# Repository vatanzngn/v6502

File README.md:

# 💻 vz6502: A Homebrew Single Board Computer Based on WDC 65C02

A custom-built single board computer (SBC) powered by the WDC 65C02 processor, featuring VGA and PS/2 interfaces, an onboard terminal, and a CPLD-based system controller.

---

## ⚙️ Specifications

- **CPU:** WDC 65C02 @ 1.8432 MHz (chosen for UART-compatible clock rate)
- **System Controller:** Altera EPM7128SLC84 CPLD
- **ROM:** Atmel 28C256 EEPROM (16 KB used)
- **RAM:** Hitachi 62256 SRAM (28 KB used)
- **Serial Interfaces:**  
  - 2× 65C51 ACIA (UART and terminal communication)
- **I/O Interface:**  
  - 1× 65C22 VIA
- **Video Output:** VGA interface  
- **Input:** PS/2 keyboard  
- **Terminal:** Atmega328P-based serial terminal

## 🧩 PCB Design

<div align="center">
  
  <p><em>Front side of the PCB</em></p>
</div>

<div align="center">
  
  <p><em>Back side of the PCB</em></p>
</div>

## 🔌 Schematic

<div align="center">
  
  <p><em>System schematic showing CPU, RAM, ROM, I/O, and video interfaces</em></p>
</div>

## 🧠 Memory Map Overview

### 📋 Detailed Address Mapping

| Unit   | First Address (bin)          | Last Address (bin)           | Address Range (Hex) | Description            | Size  |
|--------|------------------------------|------------------------------|---------------------|------------------------|-------|
| RAM    | 0000 0000 0000 0000          | 0110 1111 1111 1111          | 0000–6FFF           | System memory          | 28 KB |
| VIA0   | 0111 0000 0000 0000          | 0111 0000 0000 1100          | 7000–700C           | VIA 0 registers        | 12 B  |
| VIA1   | 0111 0001 0000 0000          | 0111 0001 0000 1100          | 7100–710C           | VIA 1 registers        | 12 B  |
| ACIA0  | 0111 0010 0000 0000          | 0111 0010 0000 0011          | 7200–7203           | ACIA 0 registers       | 4 B   |
| ACIA1  | 0111 0011 0000 0000          | 0111 0011 0000 0011          | 7300–7303           | ACIA 1 registers       | 4 B   |
| RESRV  | 0111 0100 0000 0000          | 0111 1111 1111 1111          | 7304–7FFF           | Reserved               | N/A   |
| ROM    | 1000 0000 0000 0000          | 1111 1111 1111 1111          | 8000–FFFF           | System ROM             | 32 KB |

---

## 📁 File Structure

| Folder   | Description                        |
|----------|------------------------------------|
| `/pcb`   | KiCAD PCB design files             |
| `/gerber`| Gerber files for PCB manufacturing |
| `/ext`   | GitHub assets, images, and extras  |

---
⚠️ CPLD and operating system source files will be uploaded in a future update.

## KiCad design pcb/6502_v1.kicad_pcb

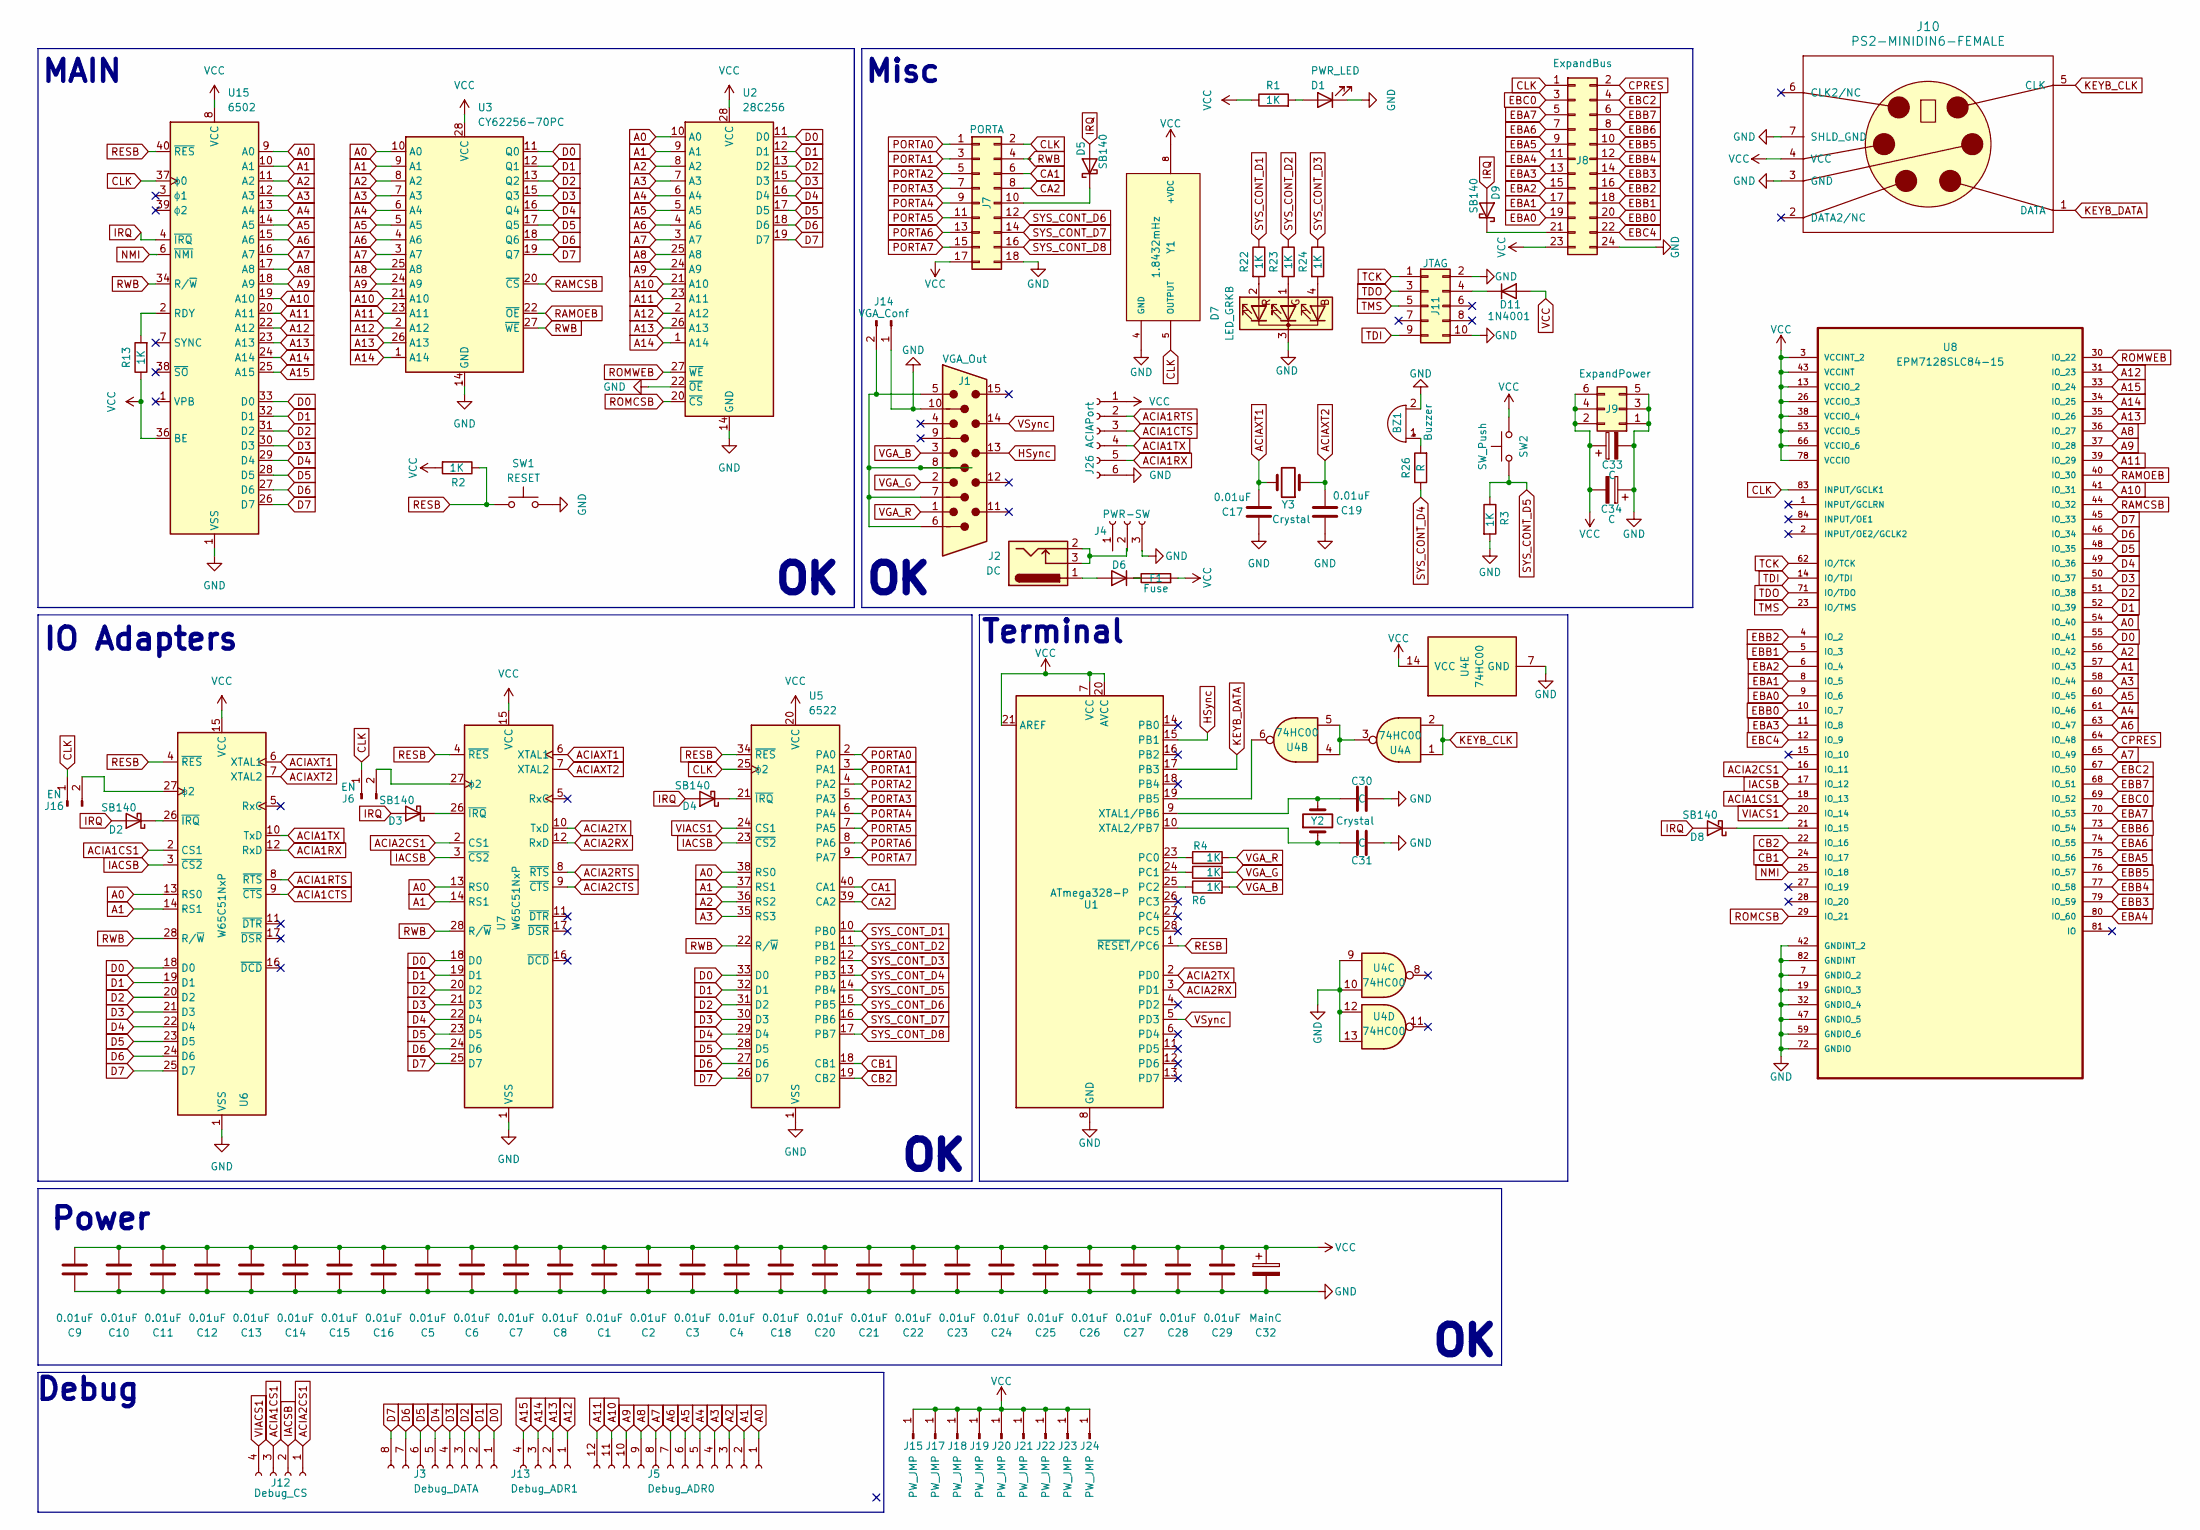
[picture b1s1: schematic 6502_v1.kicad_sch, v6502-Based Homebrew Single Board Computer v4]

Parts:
BZ1: Buzzer; Buzzer_12x9.5RM7.6
C1, C2, C3, C4, C5, C6, C7, C8, C9, C10, C11, C12, C13, C14, C15, C16, C17, C18, C19, C20, C21, C22, C23, C24, C25, C26, C27, C28, C29: 0.01uF; C_Disc_D3.4mm_W2.1mm_P2.50mm
C30, C31: C; C_Disc_D3.4mm_W2.1mm_P2.50mm
C32: MainC; CP_Radial_D5.0mm_P2.00mm
C33, C34: C; CP_Radial_D5.0mm_P2.00mm
D1: PWR_LED; LED_D5.0mm
D2, D3, D4, D5, D8, D9: SB140; D_DO-41_SOD81_P10.16mm_Horizontal
D6: D; D_DO-41_SOD81_P10.16mm_Horizontal
D7: LED_GRKB; LED_D5.0mm-4_RGB_Wide_Pins
D11: 1N4001; D_DO-41_SOD81_P10.16mm_Horizontal
F1: Fuse; Fuse_2920_7451Metric
J1: VGA_Out; DSUB-15-HD_Female_Horizontal_P2.29x1.98mm_EdgePinOffset3.03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
J2: DC; BarrelJack_GCT_DCJ200-10-A_Horizontal
J3: Debug_DATA; PinHeader_1x08_P2.54mm_Vertical
J4: PWR-SW; PinHeader_1x03_P2.54mm_Vertical
J5: Debug_ADR0; PinHeader_1x12_P2.54mm_Vertical
J6, J16: EN; SolderJumper-3_P1.3mm_Open_RoundedPad1.0x1.5mm_NumberLabels
J7: PORTA; PinSocket_2x09_P2.54mm_Horizontal
J8: ExpandBus; PinSocket_2x12_P2.54mm_Horizontal
J9: ExpandPower; PinSocket_2x03_P2.54mm_Horizontal
J10: PS2-MINIDIN6-FEMALE; MINI-DIN-6-FULL-SHIELD
J11: JTAG; PinHeader_2x05_P2.54mm_Vertical
J12: Debug_CS; PinHeader_1x04_P2.54mm_Vertical
J13: Debug_ADR1; PinHeader_1x04_P2.54mm_Vertical
J14: VGA_Conf; SolderJumper-3_P1.3mm_Open_RoundedPad1.0x1.5mm_NumberLabels
J15, J17, J18, J19, J20, J21, J22, J23, J24: PW_JMP; PinSocket_1x01_P2.54mm_Vertical
J26: ACIAPort; PinSocket_1x06_P2.54mm_Horizontal
R1, R2, R3, R4, R5, R6, R13, R22, R23, R24: 1K; R_Axial_DIN0207_L6.3mm_D2.5mm_P10.16mm_Horizontal
R26: R; R_Axial_DIN0207_L6.3mm_D2.5mm_P10.16mm_Horizontal
SW1: RESET; SW_PUSH_6mm_H4.3mm
SW2: SW_Push; SW_PUSH_6mm_H4.3mm
U1: ATmega328-P; DIP-28_W7.62mm
U2: 28C256; DIP-28_W15.24mm_Socket
U3: CY62256-70PC; DIP-28_W15.24mm_Socket
U4: 74HC00; DIP-14_W7.62mm
U5: 6522; DIP-40_W15.24mm_Socket
U6, U7: W65C51NxP; DIP-28_W15.24mm_Socket
U8: EPM7128SLC84-15; PLCC-84_THT-Socket; MPN EPM7128SLC84-15
U15: 6502; DIP-40_W15.24mm_Socket
Y1: 1.8432mHz; Oscillator_DIP-8_LargePads; PARTREV N/A
Y2: Crystal; Crystal_HC52-U_Vertical
Y3: Crystal; Crystal_HC18-U_Vertical

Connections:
A0: J5.1, U2.10 (A0), U3.10 (A0), U5.38 (RS0), U6.13 (RS0), U7.13 (RS0), U8.54 (IO_40), U15.9 (A0); also elsewhere on the board
A1: J5.2, U2.9 (A1), U3.9 (A1), U5.37 (RS1), U6.14 (RS1), U7.14 (RS1), U8.57 (IO_43), U15.10 (A1); also elsewhere on the board
A2: J5.3, U2.8 (A2), U3.8 (A2), U5.36 (RS2), U8.56 (IO_42), U15.11 (A2); also elsewhere on the board
A3: J5.4, U2.7 (A3), U3.7 (A3), U5.35 (RS3), U8.58 (IO_44), U15.12 (A3); also elsewhere on the board
A4: J5.5, U2.6 (A4), U3.6 (A4), U8.61 (IO_46), U15.13 (A4); also elsewhere on the board
A5: J5.6, U2.5 (A5), U3.5 (A5), U8.60 (IO_45), U15.14 (A5); also elsewhere on the board
A6: J5.7, U2.4 (A6), U3.4 (A6), U8.63 (IO_47), U15.15 (A6); also elsewhere on the board
A7: J5.8, U2.3 (A7), U3.3 (A7), U8.65 (IO_49), U15.16 (A7); also elsewhere on the board
A8: J5.9, U2.25 (A8), U3.25 (A8), U8.36 (IO_27), U15.17 (A8); also elsewhere on the board
A9: J5.10, U2.24 (A9), U3.24 (A9), U8.37 (IO_28), U15.18 (A9); also elsewhere on the board
A10: J5.11, U2.21 (A10), U3.21 (A10), U8.41 (IO_31), U15.19 (A10); also elsewhere on the board
A11: J5.12, U2.23 (A11), U3.23 (A11), U8.39 (IO_29), U15.20 (A11); also elsewhere on the board
A12: J13.1, U2.2 (A12), U3.2 (A12), U8.31 (IO_23), U15.22 (A12); also elsewhere on the board
A13: J13.2, U2.26 (A13), U3.26 (A13), U8.35 (IO_26), U15.23 (A13); also elsewhere on the board
A14: J13.3, U2.1 (A14), U3.1 (A14), U8.34 (IO_25), U15.24 (A14); also elsewhere on the board
A15: J13.4, U8.33 (IO_24), U15.25 (A15); also elsewhere on the board
ACIA1CS1: J12.3, U6.2 (CS1), U8.18 (IO_13); also elsewhere on the board
ACIA1CTS: J26.3, U6.9 (~CTS); also elsewhere on the board
ACIA1RTS: J26.2, U6.8 (~RTS); also elsewhere on the board
ACIA1RX: J26.5, U6.12 (RxD); also elsewhere on the board
ACIA1TX: J26.4, U6.10 (TxD); also elsewhere on the board
ACIA2CS1: J12.1, U7.2 (CS1), U8.16 (IO_11); also elsewhere on the board
ACIA2CTS: U7.9 (~CTS)
ACIA2RTS: U7.8 (~RTS)
ACIA2RX: U1.3 (PD1), U7.12 (RxD)
ACIA2TX: U1.2 (PD0), U7.10 (TxD)
ACIAXT1: C17.1, U6.6 (XTAL1), U7.6 (XTAL1), Y3.2; also elsewhere on the board
ACIAXT2: C19.1, U6.7 (XTAL2), U7.7 (XTAL2), Y3.1; also elsewhere on the board
CA1: J7.6, U5.40 (CA1)
CA2: J7.8, U5.39 (CA2)
CB1: U5.18 (CB1), U8.24 (IO_17); also elsewhere on the board
CB2: U5.19 (CB2), U8.22 (IO_16); also elsewhere on the board
CLK: J6.1, J7.2, J8.1, J16.1, U5.25 (ϕ2), U8.83 (INPUT/GCLK1), U15.37 (ϕ0), Y1.5 (OUTPUT); also elsewhere on the board
CPRES: J8.2, U8.64 (IO_48); also elsewhere on the board
D0: J3.1, U2.11 (D0), U3.11 (Q0), U5.33 (D0), U6.18 (D0), U7.18 (D0), U8.55 (IO_41), U15.33 (D0); also elsewhere on the board
D1: J3.2, U2.12 (D1), U3.12 (Q1), U5.32 (D1), U6.19 (D1), U7.19 (D1), U8.52 (IO_39), U15.32 (D1); also elsewhere on the board
D2: J3.3, U2.13 (D2), U3.13 (Q2), U5.31 (D2), U6.20 (D2), U7.20 (D2), U8.51 (IO_38), U15.31 (D2); also elsewhere on the board
D3: J3.4, U2.15 (D3), U3.15 (Q3), U5.30 (D3), U6.21 (D3), U7.21 (D3), U8.50 (IO_37), U15.30 (D3); also elsewhere on the board
D4: J3.5, U2.16 (D4), U3.16 (Q4), U5.29 (D4), U6.22 (D4), U7.22 (D4), U8.49 (IO_36), U15.29 (D4); also elsewhere on the board
D5: J3.6, U2.17 (D5), U3.17 (Q5), U5.28 (D5), U6.23 (D5), U7.23 (D5), U8.48 (IO_35), U15.28 (D5); also elsewhere on the board
D6: J3.7, U2.18 (D6), U3.18 (Q6), U5.27 (D6), U6.24 (D6), U7.24 (D6), U8.46 (IO_34), U15.27 (D6); also elsewhere on the board
D7: J3.8, U2.19 (D7), U3.19 (Q7), U5.26 (D7), U6.25 (D7), U7.25 (D7), U8.45 (IO_33), U15.26 (D7); also elsewhere on the board
EBA0: J8.19, U8.9 (IO_6); also elsewhere on the board
EBA1: J8.17, U8.8 (IO_5); also elsewhere on the board
EBA2: J8.15, U8.6 (IO_4); also elsewhere on the board
EBA3: J8.13, U8.11 (IO_8); also elsewhere on the board
EBA4: J8.11, U8.80 (IO_60); also elsewhere on the board
EBA5: J8.9, U8.75 (IO_56); also elsewhere on the board
EBA6: J8.7, U8.74 (IO_55); also elsewhere on the board
EBA7: J8.5, U8.70 (IO_53); also elsewhere on the board
EBB0: J8.20, U8.10 (IO_7); also elsewhere on the board
EBB1: J8.18, U8.5 (IO_3); also elsewhere on the board
EBB2: J8.16, U8.4 (IO_2); also elsewhere on the board
EBB3: J8.14, U8.79 (IO_59); also elsewhere on the board
EBB4: J8.12, U8.77 (IO_58); also elsewhere on the board
EBB5: J8.10, U8.76 (IO_57); also elsewhere on the board
EBB6: J8.8, U8.73 (IO_54); also elsewhere on the board
EBB7: J8.6, U8.68 (IO_51); also elsewhere on the board
EBC0: J8.3, U8.69 (IO_52); also elsewhere on the board
EBC2: J8.4, U8.67 (IO_50); also elsewhere on the board
EBC4: J8.22, U8.12 (IO_9); also elsewhere on the board
GND: BZ1.2 (+), C1.2, C2.2, C3.2, C4.2, C5.2, C6.2, C7.2, C8.2, C9.2, C10.2, C11.2, C12.2, C13.2, C14.2, C15.2, C16.2, C17.2, C18.2, C19.2, C20.2, C21.2, C22.2, C23.2, C24.2, C25.2, C26.2, C27.2, C28.2, C29.2, C30.2, C31.2, C32.2, C33.2, C34.1, D1.1 (K), D7.3 (K), J1.10, J4.3, J7.18, J8.24, J9.1, J9.3, J9.5, J10.3 (GND), J10.7 (SHLD_GND), J11.2, J11.10, J14.1, J26.6, R3.2, SW1.2, U1.8 (GND), U1.22 (GND), U2.14 (GND), U2.22 (~OE), U3.14 (GND), U4.7 (GND), U4.9, U4.10, U4.12, U4.13, U5.1 (VSS), U6.1 (VSS), U7.1 (VSS), U8.7 (GNDIO_2), U8.19 (GNDIO_3), U8.32 (GNDIO_4), U8.42 (GNDINT_2), U8.47 (GNDIO_5), U8.59 (GNDIO_6), U8.72 (GNDIO), U8.82 (GNDINT), U15.1 (VPB), U15.21 (VSS), Y1.4 (GND); also elsewhere on the board
HSync: J1.13, U1.15 (PB1)
IACSB: J12.2, U5.23 (~CS2), U6.3 (~CS2), U7.3 (~CS2), U8.17 (IO_12); also elsewhere on the board
IRQ: D2.2 (A), D3.2 (A), D4.2 (A), D5.2 (A), D8.2 (A), D9.2 (A), U15.4 (~IRQ); also elsewhere on the board
KEYB_CLK: J10.5 (CLK), U4.1, U4.2
KEYB_DATA: J10.1 (DATA), U1.17 (PB3)
unnamed: BZ1.1 (-), R26.2
unnamed 69: D1.2 (A), R1.2; also elsewhere on the board
unnamed 70: D2.1 (K), U6.26 (~IRQ); also elsewhere on the board
unnamed: D3.1 (K), U7.26 (~IRQ)
unnamed: D4.1 (K), U5.21 (~IRQ)
unnamed: D5.1 (K), J7.10
unnamed: D6.2 (A), J2.1
unnamed: D6.1 (K), F1.1
unnamed: D7.4 (BA), R24.2
unnamed: D7.1 (GA), R23.2
unnamed: D7.2 (RA), R22.2
unnamed 79: D8.1 (K), U8.21 (IO_15); also elsewhere on the board
unnamed: D9.1 (K), J8.21
unnamed 81: D11.1 (K), J11.4; also elsewhere on the board
unnamed: J2.2, J2.3, J4.2
unnamed: J6.2, U7.27 (ϕ2)
unnamed: J11.1, U8.62 (IO/TCK)
unnamed: J11.3, U8.71 (IO/TDO)
unnamed: J11.5, U8.23 (IO/TMS)
unnamed: J11.9, U8.14 (IO/TDI)
unnamed: J1.5, J1.6, J1.7, J1.8, J14.2
unnamed 89: J16.2, U6.27 (ϕ2); also elsewhere on the board
unnamed: U1.19 (PB5), U4.6
unnamed: R4.1, U1.23 (PC0)
unnamed: R5.1, U1.24 (PC1)
unnamed: R6.1, U1.25 (PC2)
unnamed: C30.1, U1.9 (XTAL1/PB6), Y2.2
unnamed: C31.1, U1.10 (XTAL2/PB7), Y2.1
unnamed: U2.20 (~CS), U8.29 (IO_21)
unnamed: U2.27 (~WE), U8.30 (IO_22)
unnamed: U3.20 (~CS), U8.44 (IO_32)
unnamed: U3.22 (~OE), U8.40 (IO_30)
unnamed: U4.3, U4.4, U4.5
unnamed: U8.25 (IO_18), U15.6 (~NMI)
unnamed 102: R13.2, U15.2 (RDY); also elsewhere on the board
PORTA0: J7.1, U5.2 (PA0)
PORTA1: J7.3, U5.3 (PA1)
PORTA2: J7.5, U5.4 (PA2)
PORTA3: J7.7, U5.5 (PA3)
PORTA4: J7.9, U5.6 (PA4)
PORTA5: J7.11, U5.7 (PA5)
PORTA6: J7.13, U5.8 (PA6)
PORTA7: J7.15, U5.9 (PA7)
RESB: R2.1, SW1.1, U1.1 (~RESET/PC6), U5.34 (~RES), U6.4 (~RES), U7.4 (~RES), U15.40 (~RES); also elsewhere on the board
RWB: J7.4, U3.27 (~WE), U5.22 (R/~W), U6.28 (R/~W), U7.28 (R/~W), U15.34 (R/~W); also elsewhere on the board
SYS_CONT_D1: R22.1, U5.10 (PB0)
SYS_CONT_D2: R23.1, U5.11 (PB1)
SYS_CONT_D3: R24.1, U5.12 (PB2)
SYS_CONT_D4: R26.1, U5.13 (PB3)
SYS_CONT_D5: R3.1, SW2.1, U5.14 (PB4)
SYS_CONT_D6: J7.12, U5.15 (PB5)
SYS_CONT_D7: J7.14, U5.16 (PB6)
SYS_CONT_D8: J7.16, U5.17 (PB7)
VCC: C1.1, C2.1, C3.1, C4.1, C5.1, C6.1, C7.1, C8.1, C9.1, C10.1, C11.1, C12.1, C13.1, C14.1, C15.1, C16.1, C18.1, C20.1, C21.1, C22.1, C23.1, C24.1, C25.1, C26.1, C27.1, C28.1, C29.1, C32.1, C33.1, C34.2, D11.2 (A), F1.2, J7.17, J8.23, J9.2, J9.4, J9.6, J10.4 (VCC), J15.1, J17.1, J18.1, J19.1, J20.1, J21.1, J22.1, J23.1, J24.1, J26.1, R1.1, R2.2, R13.1, SW2.2, U1.7 (VCC), U1.20 (AVCC), U1.21 (AREF), U2.28 (VCC), U3.28 (VCC), U4.14 (VCC), U5.20 (VCC), U6.15 (VCC), U7.15 (VCC), U8.3 (VCCINT_2), U8.13 (VCCIO_2), U8.26 (VCCIO_3), U8.38 (VCCIO_4), U8.43 (VCCINT), U8.53 (VCCIO_5), U8.66 (VCCIO_6), U8.78 (VCCIO), U15.8 (VCC), U15.36 (BE), Y1.8 (+VDC); also elsewhere on the board
VGA_B: J1.3, R6.2
VGA_G: J1.2, R5.2
VGA_R: J1.1, R4.2
VIACS1: J12.4, U5.24 (CS1), U8.20 (IO_14); also elsewhere on the board
VSync: J1.14, U1.5 (PD3)

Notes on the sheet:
Terminal
Power
MAIN
Debug
IO Adapters
Misc

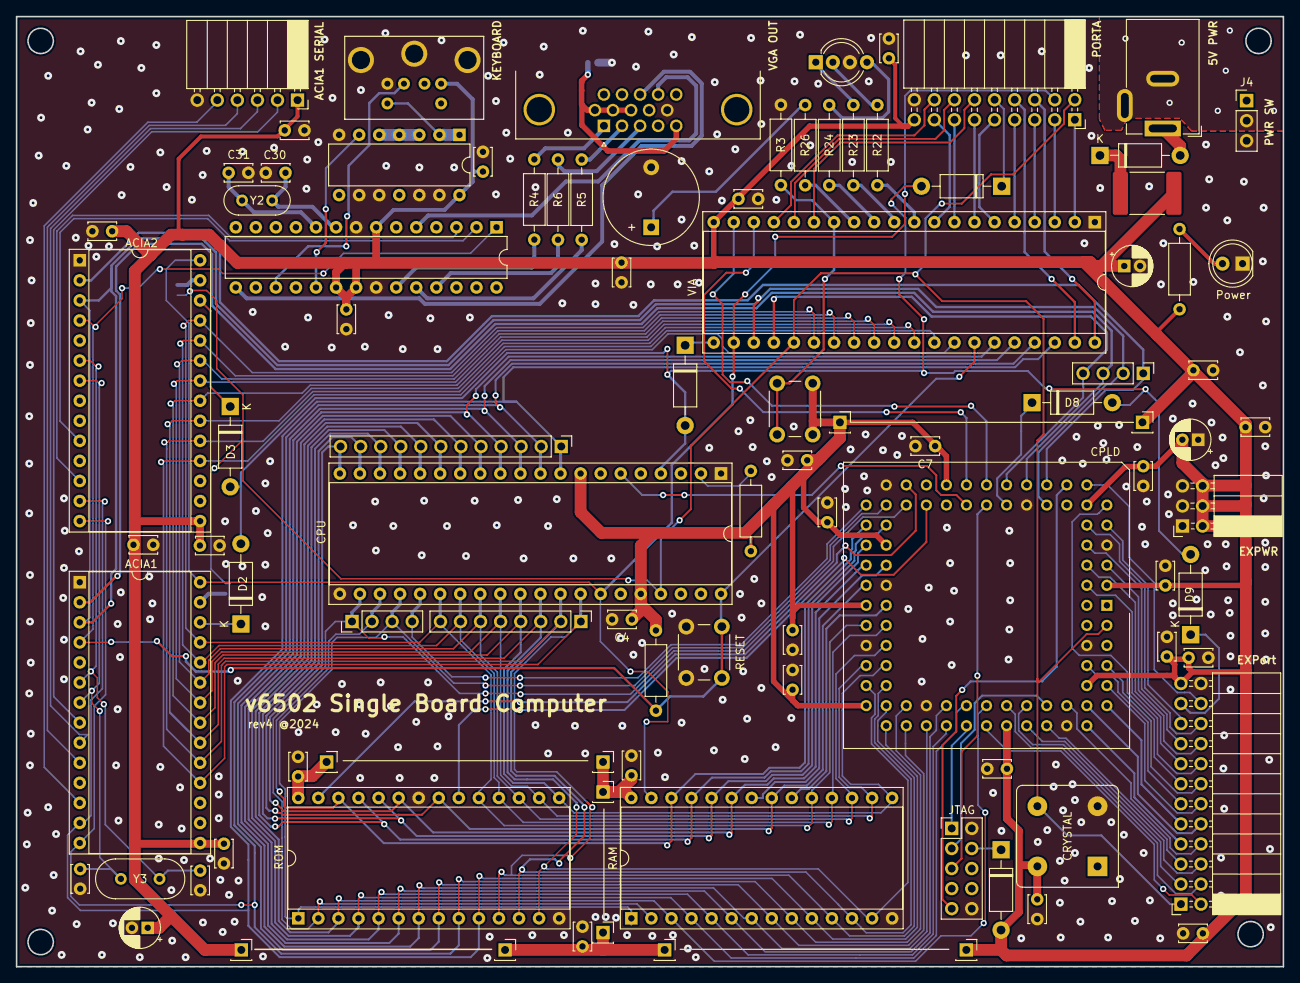
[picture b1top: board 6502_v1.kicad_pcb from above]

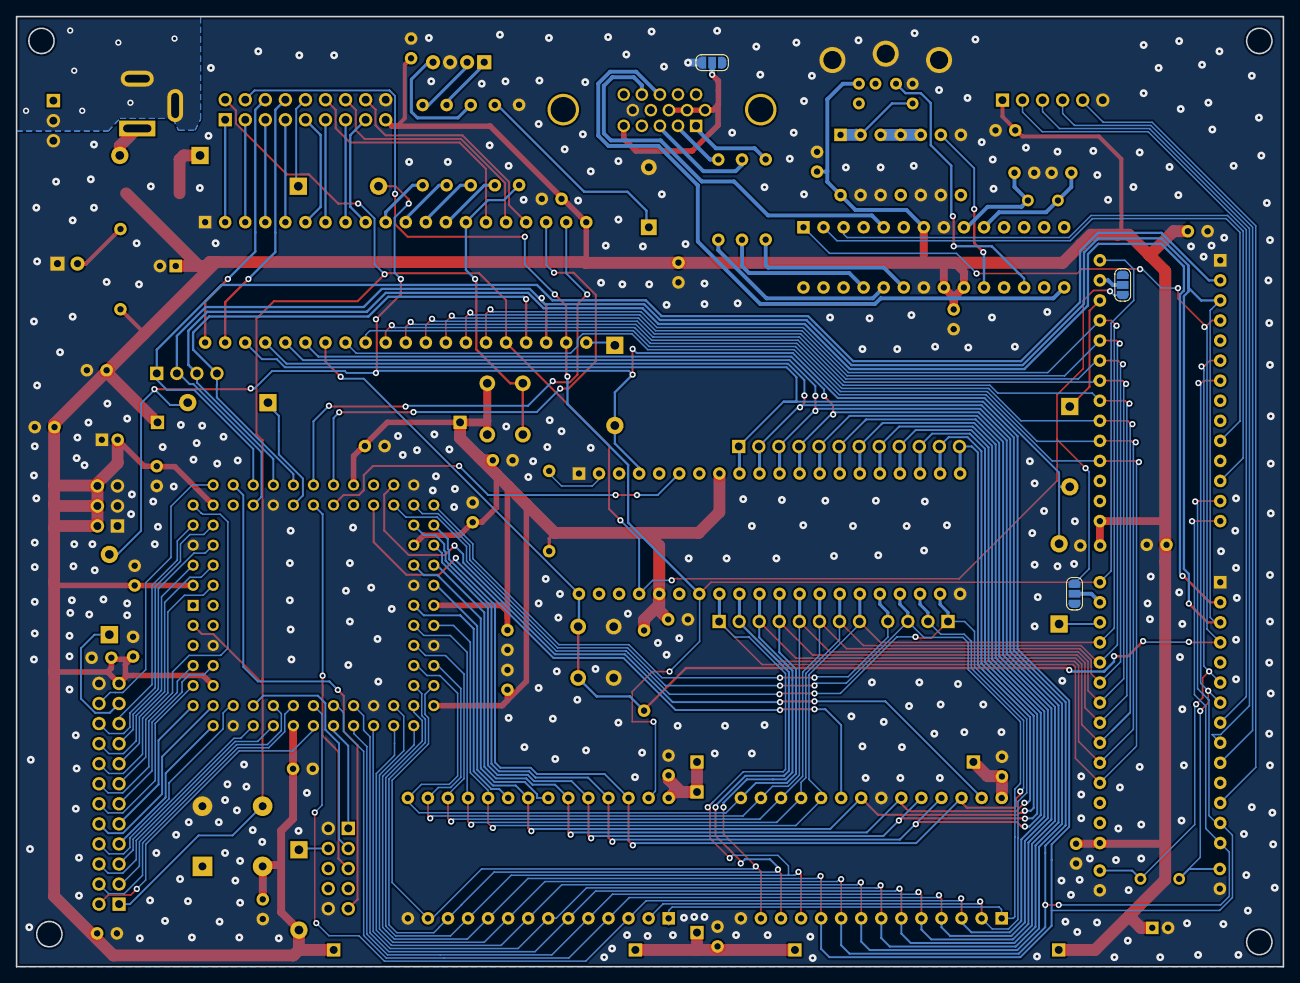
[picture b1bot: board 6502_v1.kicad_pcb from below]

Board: 2 copper layers, 160.4 x 120.3 mm, 98 parts (3 on the bottom side), 124 nets.

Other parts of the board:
ACIA1: W65C51NxP; DIP-28_W15.24mm_Socket
C2#2: 0.01uF; C_Disc_D3.4mm_W2.1mm_P2.50mm
CPLD: EPM7128SLC84-15; PLCC-84_THT-Socket
CPU: 6502; DIP-40_W15.24mm_Socket
CRYSTAL: 1.8432mHz; Oscillator_DIP-8_LargePads
J28: PW_JMP; PinSocket_1x01_P2.54mm_Vertical
JTAG: JTAG; PinHeader_2x05_P2.54mm_Vertical
Power: PWR_LED; LED_D5.0mm
RAM: CY62256-70PC; DIP-28_W15.24mm_Socket
RESET: RESET; SW_PUSH_6mm_H4.3mm
ROM: 28C256; DIP-28_W15.24mm_Socket

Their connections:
A0: ACIA1.13 (RS0), CPLD.54 (IO_40), CPU.9 (A0), RAM.10 (A0), ROM.10 (A0); also elsewhere on the board
A1: ACIA1.14 (RS1), CPLD.57 (IO_43), CPU.10 (A1), RAM.9 (A1), ROM.9 (A1); also elsewhere on the board
A2: CPLD.56 (IO_42), CPU.11 (A2), RAM.8 (A2), ROM.8 (A2); also elsewhere on the board
A3: CPLD.58 (IO_44), CPU.12 (A3), RAM.7 (A3), ROM.7 (A3); also elsewhere on the board
A4: CPLD.61 (IO_46), CPU.13 (A4), RAM.6 (A4), ROM.6 (A4); also elsewhere on the board
A5: CPLD.60 (IO_45), CPU.14 (A5), RAM.5 (A5), ROM.5 (A5); also elsewhere on the board
A6: CPLD.63 (IO_47), CPU.15 (A6), RAM.4 (A6), ROM.4 (A6); also elsewhere on the board
A7: CPLD.65 (IO_49), CPU.16 (A7), RAM.3 (A7), ROM.3 (A7); also elsewhere on the board
A8: CPLD.36 (IO_27), CPU.17 (A8), RAM.25 (A8), ROM.25 (A8); also elsewhere on the board
A9: CPLD.37 (IO_28), CPU.18 (A9), RAM.24 (A9), ROM.24 (A9); also elsewhere on the board
A10: CPLD.41 (IO_31), CPU.19 (A10), RAM.21 (A10), ROM.21 (A10); also elsewhere on the board
A11: CPLD.39 (IO_29), CPU.20 (A11), RAM.23 (A11), ROM.23 (A11); also elsewhere on the board
A12: CPLD.31 (IO_23), CPU.22 (A12), RAM.2 (A12), ROM.2 (A12); also elsewhere on the board
A13: CPLD.35 (IO_26), CPU.23 (A13), RAM.26 (A13), ROM.26 (A13); also elsewhere on the board
A14: CPLD.34 (IO_25), CPU.24 (A14), RAM.1 (A14), ROM.1 (A14); also elsewhere on the board
A15: CPLD.33 (IO_24), CPU.25 (A15); also elsewhere on the board
ACIA1CS1: ACIA1.2 (CS1), CPLD.18 (IO_13); also elsewhere on the board
ACIA1CTS: ACIA1.9 (~CTS); also elsewhere on the board
ACIA1RTS: ACIA1.8 (~RTS); also elsewhere on the board
ACIA1RX: ACIA1.12 (RxD); also elsewhere on the board
ACIA1TX: ACIA1.10 (TxD); also elsewhere on the board
ACIA2CS1: CPLD.16 (IO_11); also elsewhere on the board
ACIAXT1: ACIA1.6 (XTAL1); also elsewhere on the board
ACIAXT2: ACIA1.7 (XTAL2); also elsewhere on the board
CB1: CPLD.24 (IO_17); also elsewhere on the board
CB2: CPLD.22 (IO_16); also elsewhere on the board
CLK: CPLD.83 (INPUT/GCLK1), CPU.37 (ϕ0), CRYSTAL.5 (OUTPUT); also elsewhere on the board
CPRES: CPLD.64 (IO_48); also elsewhere on the board
D0: ACIA1.18 (D0), CPLD.55 (IO_41), CPU.33 (D0), RAM.11 (Q0), ROM.11 (D0); also elsewhere on the board
D1: ACIA1.19 (D1), CPLD.52 (IO_39), CPU.32 (D1), RAM.12 (Q1), ROM.12 (D1); also elsewhere on the board
D2: ACIA1.20 (D2), CPLD.51 (IO_38), CPU.31 (D2), RAM.13 (Q2), ROM.13 (D2); also elsewhere on the board
D3: ACIA1.21 (D3), CPLD.50 (IO_37), CPU.30 (D3), RAM.15 (Q3), ROM.15 (D3); also elsewhere on the board
D4: ACIA1.22 (D4), CPLD.49 (IO_36), CPU.29 (D4), RAM.16 (Q4), ROM.16 (D4); also elsewhere on the board
D5: ACIA1.23 (D5), CPLD.48 (IO_35), CPU.28 (D5), RAM.17 (Q5), ROM.17 (D5); also elsewhere on the board
D6: ACIA1.24 (D6), CPLD.46 (IO_34), CPU.27 (D6), RAM.18 (Q6), ROM.18 (D6); also elsewhere on the board
D7: ACIA1.25 (D7), CPLD.45 (IO_33), CPU.26 (D7), RAM.19 (Q7), ROM.19 (D7); also elsewhere on the board
EBA0: CPLD.9 (IO_6); also elsewhere on the board
EBA1: CPLD.8 (IO_5); also elsewhere on the board
EBA2: CPLD.6 (IO_4); also elsewhere on the board
EBA3: CPLD.11 (IO_8); also elsewhere on the board
EBA4: CPLD.80 (IO_60); also elsewhere on the board
EBA5: CPLD.75 (IO_56); also elsewhere on the board
EBA6: CPLD.74 (IO_55); also elsewhere on the board
EBA7: CPLD.70 (IO_53); also elsewhere on the board
EBB0: CPLD.10 (IO_7); also elsewhere on the board
EBB1: CPLD.5 (IO_3); also elsewhere on the board
EBB2: CPLD.4 (IO_2); also elsewhere on the board
EBB3: CPLD.79 (IO_59); also elsewhere on the board
EBB4: CPLD.77 (IO_58); also elsewhere on the board
EBB5: CPLD.76 (IO_57); also elsewhere on the board
EBB6: CPLD.73 (IO_54); also elsewhere on the board
EBB7: CPLD.68 (IO_51); also elsewhere on the board
EBC0: CPLD.69 (IO_52); also elsewhere on the board
EBC2: CPLD.67 (IO_50); also elsewhere on the board
EBC4: CPLD.12 (IO_9); also elsewhere on the board
GND: ACIA1.1 (VSS), C2#2.2, CPLD.7 (GNDIO_2), CPLD.19 (GNDIO_3), CPLD.32 (GNDIO_4), CPLD.42 (GNDINT_2), CPLD.47 (GNDIO_5), CPLD.59 (GNDIO_6), CPLD.72 (GNDIO), CPLD.82 (GNDINT), CPU.1 (VSS), CPU.21 (VSS), CRYSTAL.4 (GND), JTAG.2, JTAG.10, Power.1 (K), RAM.14 (GND), RESET.2, ROM.14 (GND), ROM.22 (~OE); also elsewhere on the board
IACSB: ACIA1.3 (~CS2), CPLD.17 (IO_12); also elsewhere on the board
IRQ: CPU.4 (~IRQ); also elsewhere on the board
NMI: CPLD.25 (IO_18), CPU.6 (~NMI)
unnamed 69: Power.2 (A); also elsewhere on the board
unnamed 70: ACIA1.26 (~IRQ); also elsewhere on the board
unnamed 79: CPLD.21 (IO_15); also elsewhere on the board
unnamed 81: JTAG.4; also elsewhere on the board
unnamed 89: ACIA1.27 (ϕ2); also elsewhere on the board
unnamed 102: CPU.2 (RDY); also elsewhere on the board
RAMCSB: CPLD.44 (IO_32), RAM.20 (~CS)
RAMOEB: CPLD.40 (IO_30), RAM.22 (~OE)
RESB: ACIA1.4 (~RES), CPU.40 (~RES), RESET.1; also elsewhere on the board
ROMCSB: CPLD.29 (IO_21), ROM.20 (~CS)
ROMWEB: CPLD.30 (IO_22), ROM.27 (~WE)
RWB: ACIA1.28 (R/~W), CPU.34 (R/~W), RAM.27 (~WE); also elsewhere on the board
TCK: CPLD.62 (IO/TCK), JTAG.1
TDI: CPLD.14 (IO/TDI), JTAG.9
TDO: CPLD.71 (IO/TDO), JTAG.3
TMS: CPLD.23 (IO/TMS), JTAG.5
VCC: ACIA1.15 (VCC), C2#2.1, CPLD.3 (VCCINT_2), CPLD.13 (VCCIO_2), CPLD.26 (VCCIO_3), CPLD.38 (VCCIO_4), CPLD.43 (VCCINT), CPLD.53 (VCCIO_5), CPLD.66 (VCCIO_6), CPLD.78 (VCCIO), CPU.8 (VCC), CPU.36 (BE), CRYSTAL.8 (+VDC), J28.1, RAM.28 (VCC), ROM.28 (VCC); also elsewhere on the board
VIACS1: CPLD.20 (IO_14); also elsewhere on the board

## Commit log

2024-05-19 Upload PCB Files.
2024-11-30 V4 Pcb Upload.
2024-11-30 v4 Gerber File Upload
2024-11-30 Picture Update
2024-12-01 Silkscreen Update
2025-05-03 Rename and readme update.

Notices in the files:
pcb/6502_v1.kicad_sch:
Copyright Vatan Zengin
